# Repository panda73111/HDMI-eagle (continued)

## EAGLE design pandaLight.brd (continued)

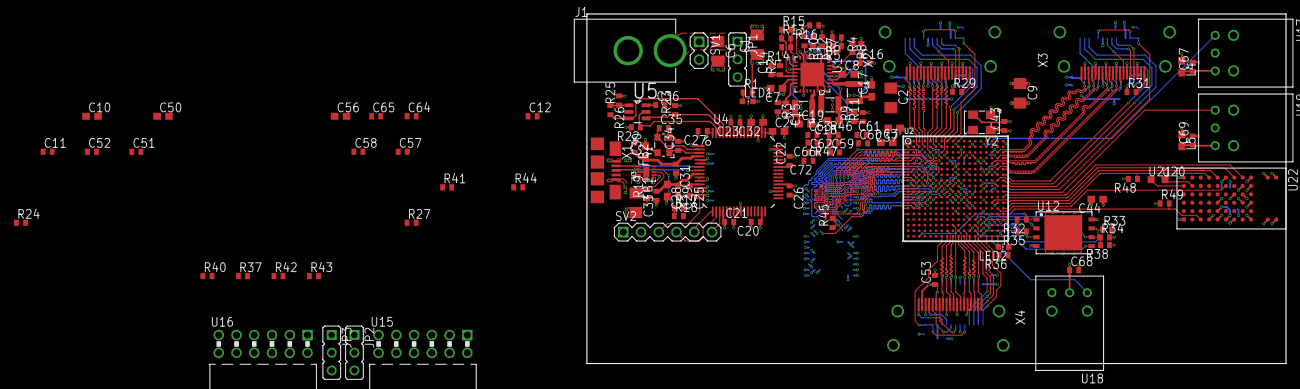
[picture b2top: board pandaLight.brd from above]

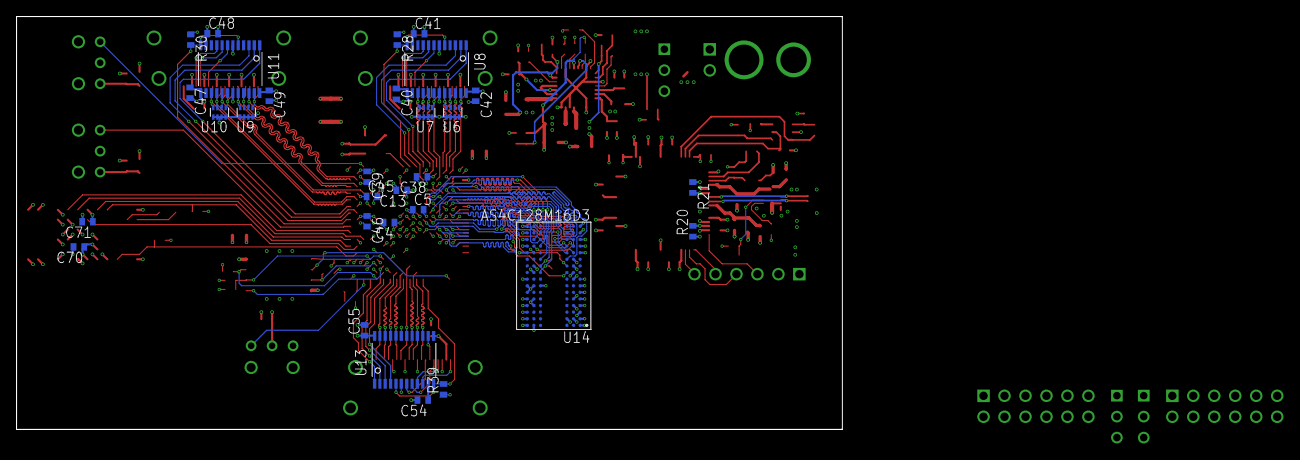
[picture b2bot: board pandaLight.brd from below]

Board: 4 copper layers, 100.0 x 50.0 mm, 164 parts (30 on the bottom side), 172 nets.

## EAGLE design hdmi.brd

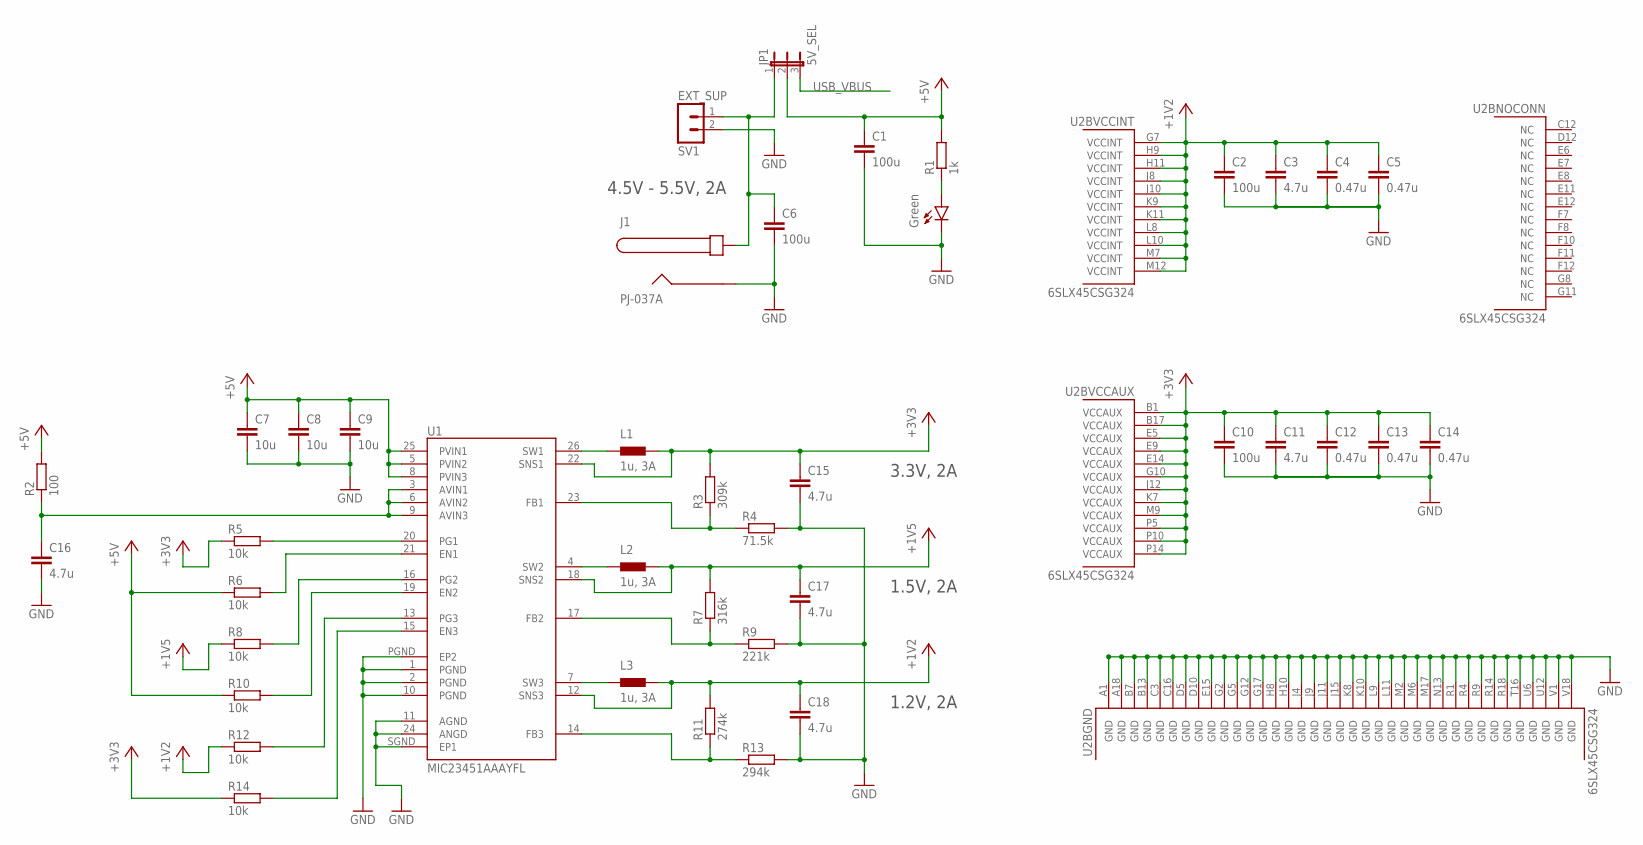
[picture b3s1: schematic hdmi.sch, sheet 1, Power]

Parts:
C1, C2, C6, C10: 100u; 1206
C3, C11, C15, C16, C17, C18: 4.7u; 0402
C4, C5, C12, C13, C14: 0.47u; 0402
C7, C8, C9: 10u; 0402
J1: PJ-037A
JP1: 5V_SEL; JP2
L1, L2, L3: 1u, 3A; 1008
LED1: Green; LED-0603
R1: 1k; 0402
R2: 100; 0402
R3: 309k; 0402
R4: 71.5k; 0402
R5, R6, R8, R10, R12, R14: 10k; 0402
R7: 316k; 0402
R9: 221k; 0402
R11: 274k; 0402
R13: 294k; 0402
SV1: EXT_SUP; MA02-1
U1: MIC23451AAAYFL; QFN-26-4X4
U2: 6SLX45CSG324; CS324

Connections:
+1V2: C2.1, C3.1, C4.1, C5.1, C18.1, L3.2, R11.2, R12.1, U1.12 (SNS3), U2.G7 (VCCINT), U2.H9 (VCCINT), U2.H11 (VCCINT), U2.J8 (VCCINT), U2.J10 (VCCINT), U2.K9 (VCCINT), U2.K11 (VCCINT), U2.L8 (VCCINT), U2.L10 (VCCINT), U2.M7 (VCCINT), U2.M12 (VCCINT)
+1V5: C17.1, L2.2, R7.2, R8.1, U1.18 (SNS2); also elsewhere on the board
+3V3: C10.1, C11.1, C12.1, C13.1, C14.1, C15.1, L1.2, R3.2, R5.1, R14.1, U1.22 (SNS1), U2.B1 (VCCAUX), U2.B17 (VCCAUX), U2.E5 (VCCAUX), U2.E9 (VCCAUX), U2.E14 (VCCAUX), U2.G10 (VCCAUX), U2.J12 (VCCAUX), U2.K7 (VCCAUX), U2.M9 (VCCAUX), U2.P5 (VCCAUX), U2.P10 (VCCAUX), U2.P14 (VCCAUX); also elsewhere on the board
+5V: C1.1, C7.1, C8.1, C9.1, JP1.2, R1.2, R2.2, R6.1, R10.1, U1.5 (PVIN2), U1.8 (PVIN3), U1.25 (PVIN1); also elsewhere on the board
CENTER: C6.1, J1.CENTER, JP1.1, SV1.1
GND: C1.2, C2.2, C3.2, C4.2, C5.2, C6.2, C7.2, C8.2, C9.2, C10.2, C11.2, C12.2, C13.2, C14.2, C15.2, C16.2, C17.2, C18.2, J1.BARREL, LED1.C, R4.2, R9.2, R13.2, SV1.2, U1.1 (PGND), U1.2 (PGND), U1.10 (PGND), U1.11 (AGND), U1.24 (ANGD), U1.PGND (EP2), U1.SGND (EP1), U2.A1 (GND), U2.A18 (GND), U2.B7 (GND), U2.B13 (GND), U2.C3 (GND), U2.C16 (GND), U2.D5 (GND), U2.D10 (GND), U2.E15 (GND), U2.G2 (GND), U2.G5 (GND), U2.G12 (GND), U2.G17 (GND), U2.H8 (GND), U2.H10 (GND), U2.J4 (GND), U2.J9 (GND), U2.J11 (GND), U2.J15 (GND), U2.K8 (GND), U2.K10 (GND), U2.L9 (GND), U2.L11 (GND), U2.M2 (GND), U2.M6 (GND), U2.M17 (GND), U2.N13 (GND), U2.R1 (GND), U2.R4 (GND), U2.R9 (GND), U2.R14 (GND), U2.R18 (GND), U2.T16 (GND), U2.U6 (GND), U2.U12 (GND), U2.V1 (GND), U2.V18 (GND); also elsewhere on the board
unnamed: L1.1, U1.26 (SW1)
unnamed: C16.1, R2.1, U1.3 (AVIN1), U1.6 (AVIN2), U1.9 (AVIN3)
unnamed: L2.1, U1.4 (SW2)
unnamed: L3.1, U1.7 (SW3)
unnamed: R11.1, R13.1, U1.14 (FB3)
unnamed: R8.2, U1.16 (PG2)
unnamed: R3.1, R4.1, U1.23 (FB1)
unnamed: R5.2, U1.20 (PG1)
unnamed: R7.1, R9.1, U1.17 (FB2)
unnamed: R10.2, U1.19 (EN2)
unnamed: R6.2, U1.21 (EN1)
unnamed: R12.2, U1.13 (PG3)
unnamed: R14.2, U1.15 (EN3)
unnamed: LED1.A, R1.1
USB_VBUS: JP1.3; also elsewhere on the board

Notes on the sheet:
4.5V - 5.5V, 2A
3.3V, 2A
1.5V, 2A
1.2V, 2A

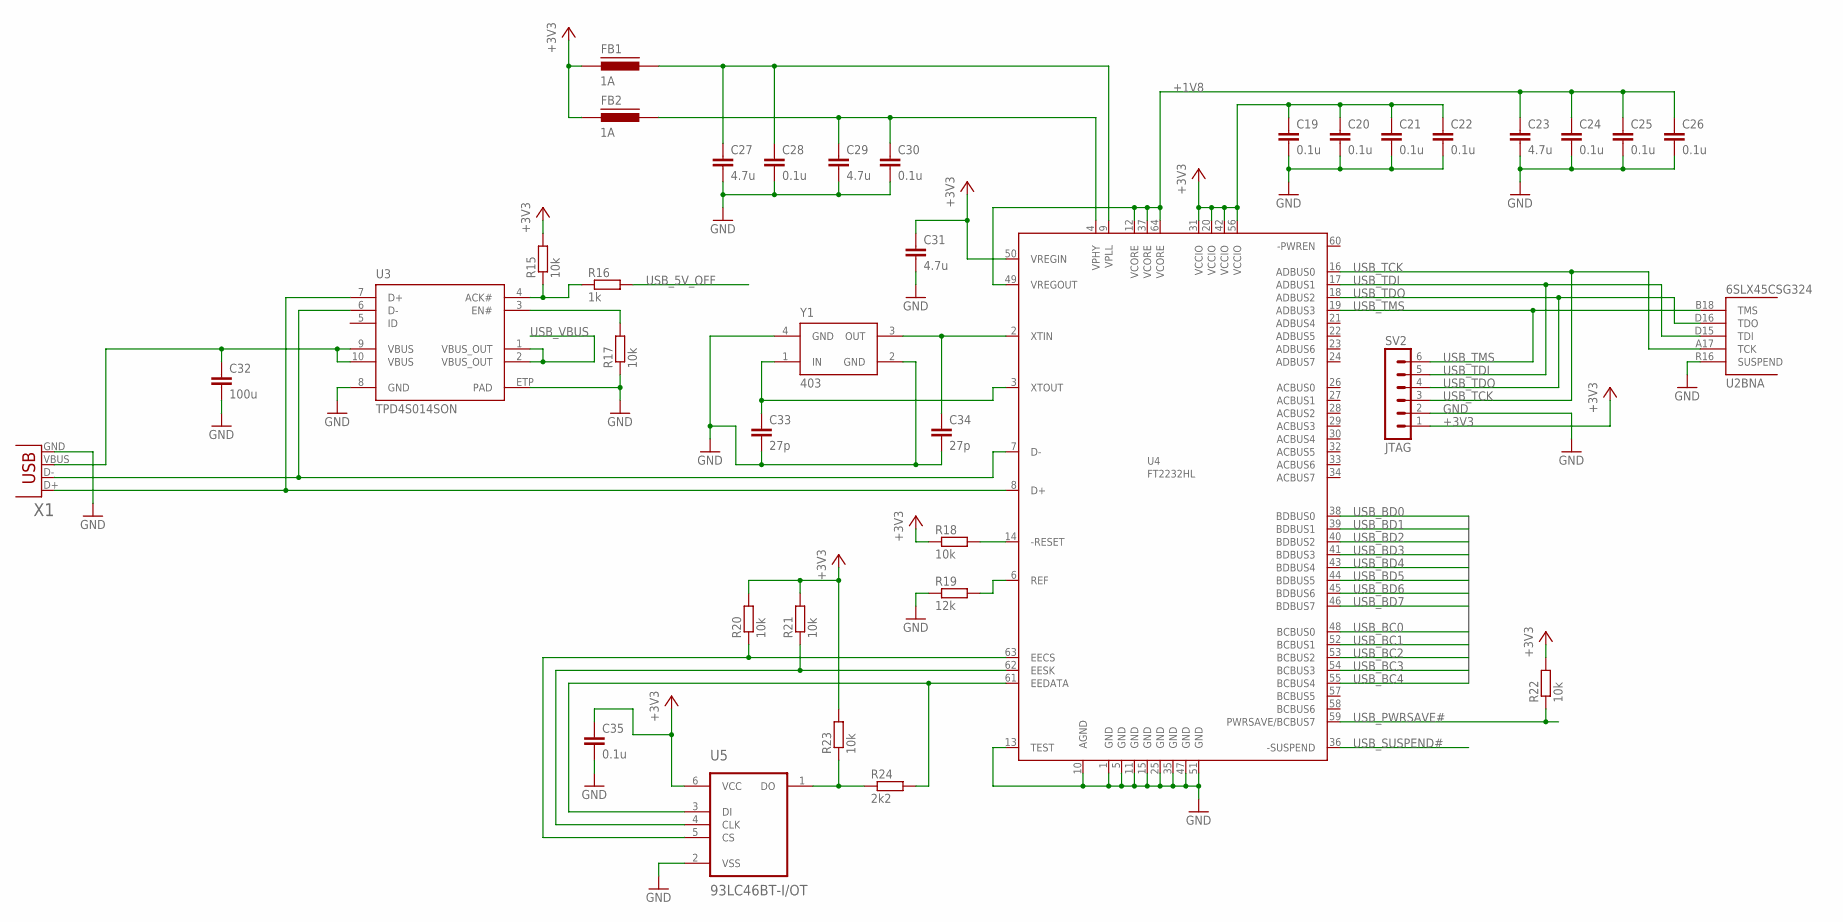
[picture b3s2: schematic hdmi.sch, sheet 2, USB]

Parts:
C19, C20, C21, C22, C24, C25, C26, C28, C30, C35: 0.1u; 0402
C23, C27, C29, C31: 4.7u; 0402
C32: 100u; 1206
C33, C34: 27p; 0402
FB1, FB2: 1A; 0402
R15, R17, R18, R20, R21, R22, R23: 10k; 0402
R16: 1k; 0402
R19: 12k; 0402
R24: 2k2; 0402
SV2: JTAG; MA06-1
U2: 6SLX45CSG324; CS324
U3: TPD4S014SON; SON10
U4: FT2232HL; LQFP64
U5: 93LC46BT-I/OT; SOT23-6
X1: USBUB-S; USB-UB-S
Y1: 403; 403-3.2X2.5

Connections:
+1V8: C23.1, C24.1, C25.1, C26.1, U4.12 (VCORE), U4.37 (VCORE), U4.49 (VREGOUT), U4.64 (VCORE)
+3V3: C19.1, C20.1, C21.1, C22.1, C31.1, C35.1, FB1.1, FB2.1, R15.2, R18.1, R20.2, R21.2, R22.2, R23.2, SV2.1, U4.20 (VCCIO), U4.31 (VCCIO), U4.42 (VCCIO), U4.50 (VREGIN), U4.56 (VCCIO), U5.6 (VCC); also elsewhere on the board
GND: C19.2, C20.2, C21.2, C22.2, C23.2, C24.2, C25.2, C26.2, C27.2, C28.2, C29.2, C30.2, C31.2, C32.2, C33.2, C34.2, C35.2, R17.1, R19.1, SV2.2, U2.R16 (SUSPEND), U3.8 (GND), U3.ETP (PAD), U4.1 (GND), U4.5 (GND), U4.10 (AGND), U4.11 (GND), U4.13 (TEST), U4.15 (GND), U4.25 (GND), U4.35 (GND), U4.47 (GND), U4.51 (GND), U5.2 (VSS), X1.GND, Y1.2 (GND), Y1.4 (GND); also elsewhere on the board
unnamed: C34.1, U4.2 (XTIN), Y1.3 (OUT)
unnamed: C33.1, U4.3 (XTOUT), Y1.1 (IN)
unnamed: R20.1, U4.63 (EECS), U5.5 (CS)
unnamed: U3.6 (D-), U4.7 (D-), X1.D-
unnamed: U3.7 (D+), U4.8 (D+), X1.D+
unnamed: R21.1, U4.62 (EESK), U5.4 (CLK)
unnamed: R24.2, U4.61 (EEDATA), U5.3 (DI)
unnamed: R19.2, U4.6 (REF)
unnamed: R23.1, R24.1, U5.1 (DO)
unnamed: R18.2, U4.14 (-RESET)
unnamed: C29.1, C30.1, FB2.2, U4.4 (VPHY)
unnamed: C27.1, C28.1, FB1.2, U4.9 (VPLL)
unnamed: C32.1, U3.9 (VBUS), U3.10 (VBUS), X1.VBUS
USB_5V_ACK#: R15.1, R16.1, U3.4 (ACK#)
USB_5V_DISABLE: R17.2, U3.3 (EN#)
USB_5V_OFF: R16.2; also elsewhere on the board
USB_BC0: U4.48 (BCBUS0); also elsewhere on the board
USB_BC1: U4.52 (BCBUS1); also elsewhere on the board
USB_BC2: U4.53 (BCBUS2); also elsewhere on the board
USB_BC3: U4.54 (BCBUS3); also elsewhere on the board
USB_BC4: U4.55 (BCBUS4); also elsewhere on the board
USB_BD0: U4.38 (BDBUS0); also elsewhere on the board
USB_BD1: U4.39 (BDBUS1); also elsewhere on the board
USB_BD2: U4.40 (BDBUS2); also elsewhere on the board
USB_BD3: U4.41 (BDBUS3); also elsewhere on the board
USB_BD4: U4.43 (BDBUS4); also elsewhere on the board
USB_BD5: U4.44 (BDBUS5); also elsewhere on the board
USB_BD6: U4.45 (BDBUS6); also elsewhere on the board
USB_BD7: U4.46 (BDBUS7); also elsewhere on the board
USB_PWRSAVE#: R22.1, U4.59 (PWRSAVE/BCBUS7)
USB_SUSPEND#: U4.36 (-SUSPEND); also elsewhere on the board
USB_TCK: SV2.3, U2.A17 (TCK), U4.16 (ADBUS0)
USB_TDI: SV2.5, U2.D15 (TDI), U4.17 (ADBUS1)
USB_TDO: SV2.4, U2.D16 (TDO), U4.18 (ADBUS2)
USB_TMS: SV2.6, U2.B18 (TMS), U4.19 (ADBUS3)
USB_VBUS: U3.1 (VBUS_OUT), U3.2 (VBUS_OUT); also elsewhere on the board

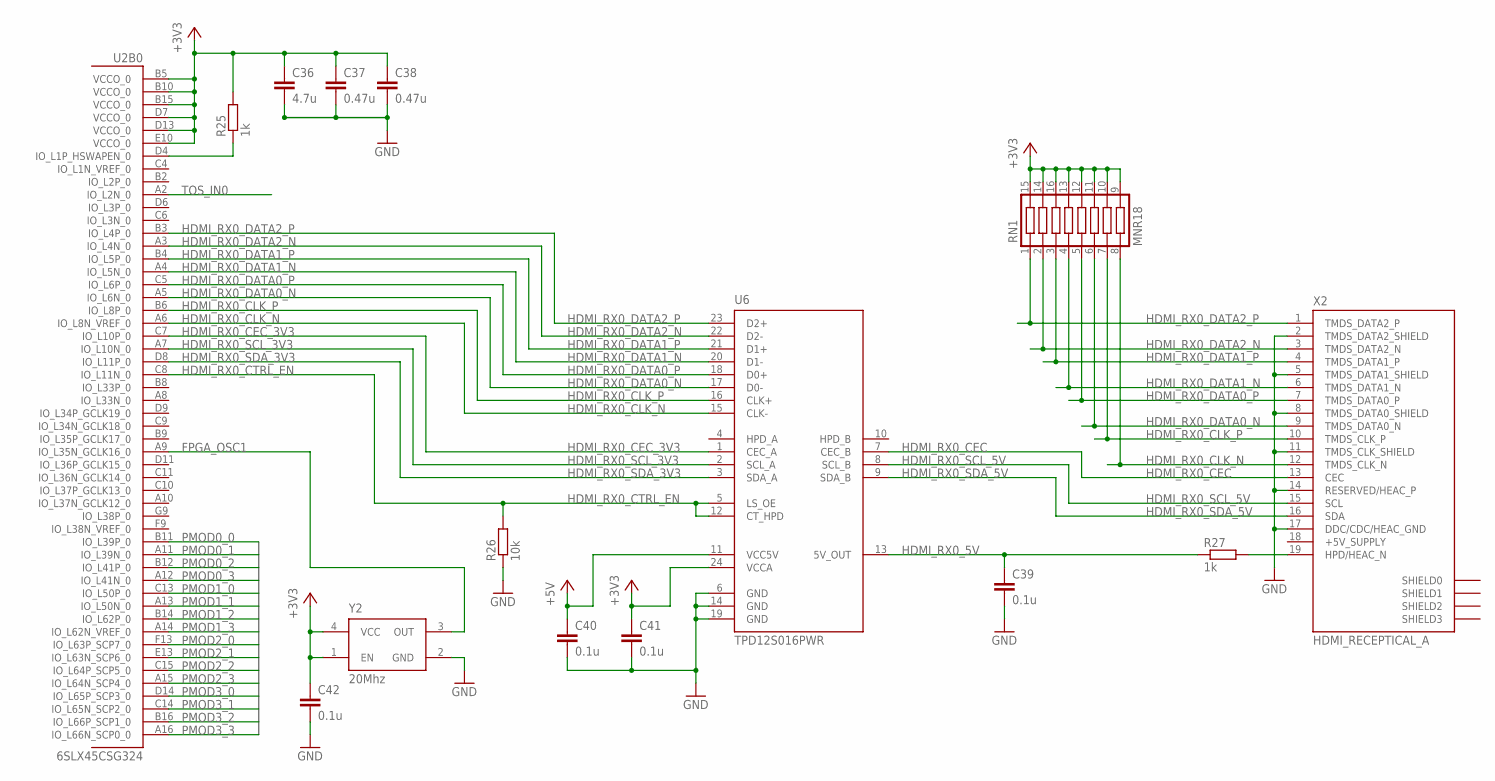
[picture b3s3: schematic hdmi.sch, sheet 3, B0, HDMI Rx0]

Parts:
C36: 4.7u; 0402
C37, C38: 0.47u; 0402
C39, C40, C41, C42: 0.1u; 0402
R25, R27: 1k; 0402
R26: 10k; 0402
RN1: MNR18
U2: 6SLX45CSG324; CS324
U6: TPD12S016PWR; PW_R-PDSO-G24
X2: HDMI_RECEPTICAL_A; HDMI_TYPE_A_RECEPTICAL
Y2: 20Mhz; 636

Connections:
+3V3: C36.1, C37.1, C38.1, C41.1, C42.1, R25.2, RN1.9, RN1.10, RN1.11, RN1.12, RN1.13, RN1.14 (15), RN1.15 (16), RN1.16 (C3), U2.B5 (VCCO_0), U2.B10 (VCCO_0), U2.B15 (VCCO_0), U2.D7 (VCCO_0), U2.D13 (VCCO_0), U2.E10 (VCCO_0), U6.24 (VCCA), Y2.1 (EN), Y2.4 (VCC); also elsewhere on the board
+5V: C40.1, U6.11 (VCC5V); also elsewhere on the board
+5V_SUPPLY: X2.18 (+5V_SUPPLY); also elsewhere on the board
FPGA_OSC1: U2.A9 (IO_L35N_GCLK16_0), Y2.3 (OUT)
GND: C36.2, C37.2, C38.2, C39.2, C40.2, C41.2, C42.2, R26.1, U6.6 (GND), U6.14 (GND), U6.19 (GND), X2.2 (TMDS_DATA2_SHIELD), X2.5 (TMDS_DATA1_SHIELD), X2.8 (TMDS_DATA0_SHIELD), X2.11 (TMDS_CLK_SHIELD), X2.14 (RESERVED/HEAC_P), X2.17 (DDC/CDC/HEAC_GND), Y2.2 (GND); also elsewhere on the board
HDMI_RX0_5V: C39.1, R27.1, U6.13 (5V_OUT)
HDMI_RX0_CEC: U6.7 (CEC_B), X2.13 (CEC)
HDMI_RX0_CEC_3V3: U2.C7 (IO_L10P_0), U6.1 (CEC_A)
HDMI_RX0_CLK_N: RN1.8, U2.A6 (IO_L8N_VREF_0), U6.15 (CLK-), X2.12 (TMDS_CLK_N)
HDMI_RX0_CLK_P: RN1.7, U2.B6 (IO_L8P_0), U6.16 (CLK+), X2.10 (TMDS_CLK_P)
HDMI_RX0_CTRL_EN: R26.2, U2.C8 (IO_L11N_0), U6.5 (LS_OE), U6.12 (CT_HPD)
HDMI_RX0_DATA0_N: RN1.6, U2.A5 (IO_L6N_0), U6.17 (D0-), X2.9 (TMDS_DATA0_N)
HDMI_RX0_DATA0_P: RN1.5, U2.C5 (IO_L6P_0), U6.18 (D0+), X2.7 (TMDS_DATA0_P)
HDMI_RX0_DATA1_N: RN1.4, U2.A4 (IO_L5N_0), U6.20 (D1-), X2.6 (TMDS_DATA1_N)
HDMI_RX0_DATA1_P: RN1.3, U2.B4 (IO_L5P_0), U6.21 (D1+), X2.4 (TMDS_DATA1_P)
HDMI_RX0_DATA2_N: RN1.2, U2.A3 (IO_L4N_0), U6.22 (D2-), X2.3 (TMDS_DATA2_N)
HDMI_RX0_DATA2_P: RN1.1, U2.B3 (IO_L4P_0), U6.23 (D2+), X2.1 (TMDS_DATA2_P)
HDMI_RX0_SCL_3V3: U2.A7 (IO_L10N_0), U6.2 (SCL_A)
HDMI_RX0_SCL_5V: U6.8 (SCL_B), X2.15 (SCL)
HDMI_RX0_SDA_3V3: U2.D8 (IO_L11P_0), U6.3 (SDA_A)
HDMI_RX0_SDA_5V: U6.9 (SDA_B), X2.16 (SDA)
unnamed: R25.1, U2.D4 (IO_L1P_HSWAPEN_0)
unnamed: R27.2, X2.19 (HPD/HEAC_N)
PMOD0_0: U2.B11 (IO_L39P_0); also elsewhere on the board
PMOD0_1: U2.A11 (IO_L39N_0); also elsewhere on the board
PMOD0_2: U2.B12 (IO_L41P_0); also elsewhere on the board
PMOD0_3: U2.A12 (IO_L41N_0); also elsewhere on the board
PMOD1_0: U2.C13 (IO_L50P_0); also elsewhere on the board
PMOD1_1: U2.A13 (IO_L50N_0); also elsewhere on the board
PMOD1_2: U2.B14 (IO_L62P_0); also elsewhere on the board
PMOD1_3: U2.A14 (IO_L62N_VREF_0); also elsewhere on the board
PMOD2_0: U2.F13 (IO_L63P_SCP7_0); also elsewhere on the board
PMOD2_1: U2.E13 (IO_L63N_SCP6_0); also elsewhere on the board
PMOD2_2: U2.C15 (IO_L64P_SCP5_0); also elsewhere on the board
PMOD2_3: U2.A15 (IO_L64N_SCP4_0); also elsewhere on the board
PMOD3_0: U2.D14 (IO_L65P_SCP3_0); also elsewhere on the board
PMOD3_1: U2.C14 (IO_L65N_SCP2_0); also elsewhere on the board
PMOD3_2: U2.B16 (IO_L66P_SCP1_0); also elsewhere on the board
PMOD3_3: U2.A16 (IO_L66N_SCP0_0); also elsewhere on the board
TOS_IN0: U2.A2 (IO_L2N_0); also elsewhere on the board

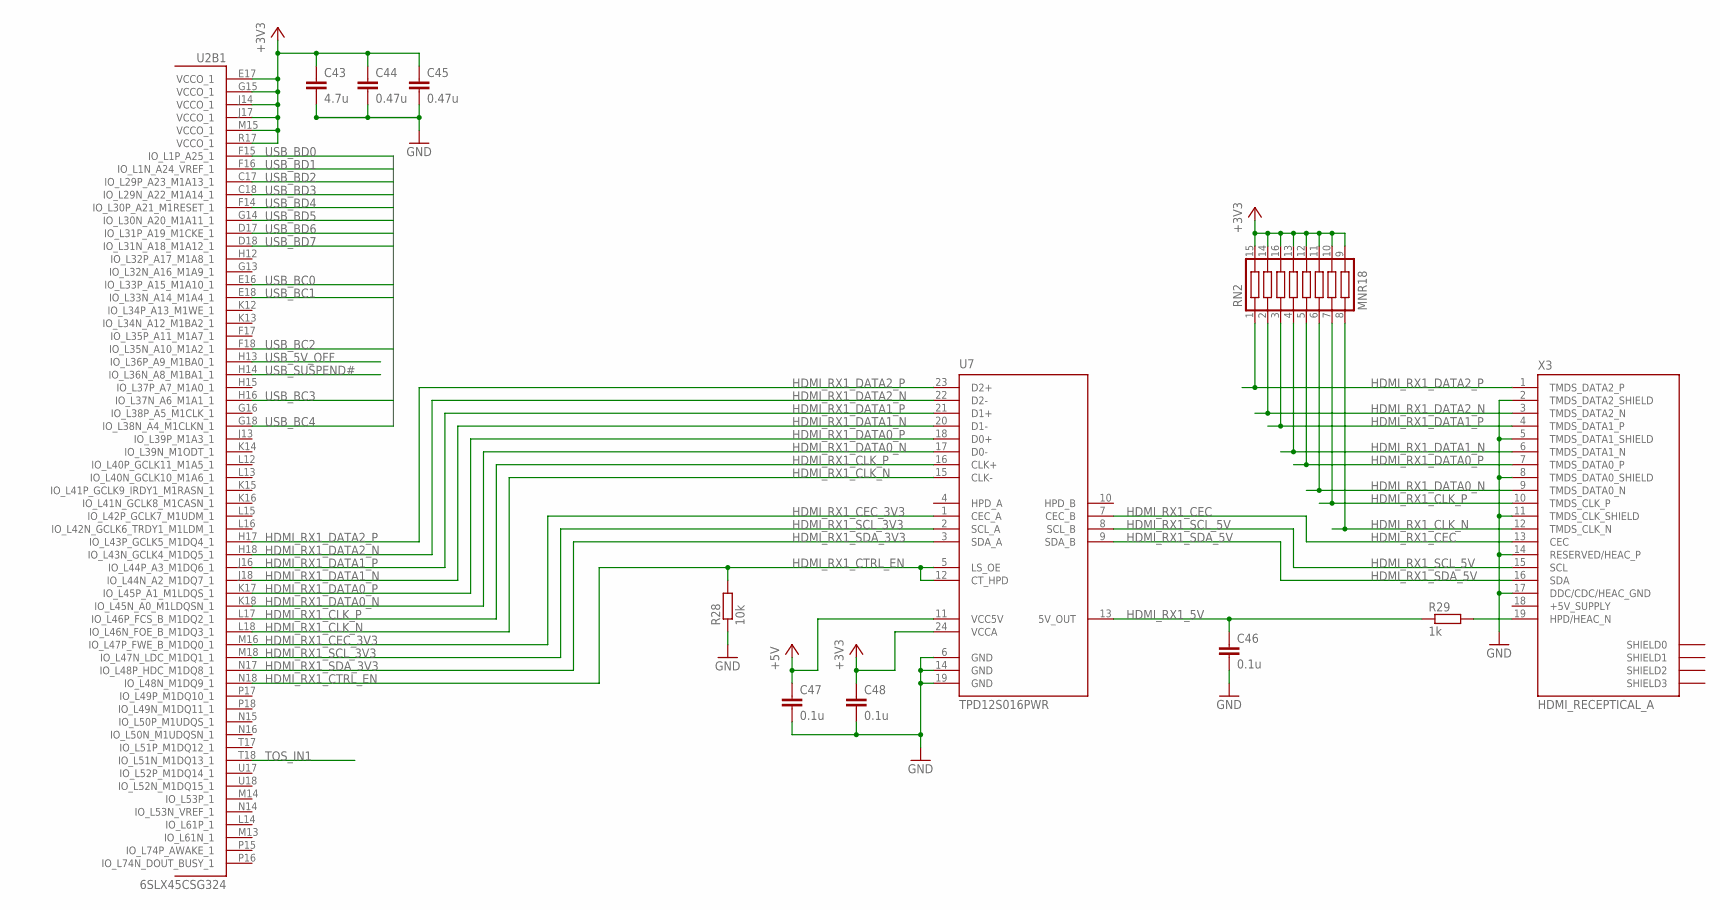
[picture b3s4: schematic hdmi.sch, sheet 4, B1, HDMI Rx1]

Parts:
C43: 4.7u; 0402
C44, C45: 0.47u; 0402
C46, C47, C48: 0.1u; 0402
R28: 10k; 0402
R29: 1k; 0402
RN2: MNR18
U2: 6SLX45CSG324; CS324
U7: TPD12S016PWR; PW_R-PDSO-G24
X3: HDMI_RECEPTICAL_A; HDMI_TYPE_A_RECEPTICAL

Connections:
+3V3: C43.1, C44.1, C45.1, C48.1, RN2.9, RN2.10, RN2.11, RN2.12, RN2.13, RN2.14 (15), RN2.15 (16), RN2.16 (C3), U2.E17 (VCCO_1), U2.G15 (VCCO_1), U2.J14 (VCCO_1), U2.J17 (VCCO_1), U2.M15 (VCCO_1), U2.R17 (VCCO_1), U7.24 (VCCA); also elsewhere on the board
+5V: C47.1, U7.11 (VCC5V); also elsewhere on the board
+5V_SUPPLY: X3.18 (+5V_SUPPLY); also elsewhere on the board
GND: C43.2, C44.2, C45.2, C46.2, C47.2, C48.2, R28.1, U7.6 (GND), U7.14 (GND), U7.19 (GND), X3.2 (TMDS_DATA2_SHIELD), X3.5 (TMDS_DATA1_SHIELD), X3.8 (TMDS_DATA0_SHIELD), X3.11 (TMDS_CLK_SHIELD), X3.14 (RESERVED/HEAC_P), X3.17 (DDC/CDC/HEAC_GND); also elsewhere on the board
HDMI_RX1_5V: C46.1, R29.1, U7.13 (5V_OUT)
HDMI_RX1_CEC: U7.7 (CEC_B), X3.13 (CEC)
HDMI_RX1_CEC_3V3: U2.M16 (IO_L47P_FWE_B_M1DQ0_1), U7.1 (CEC_A)
HDMI_RX1_CLK_N: RN2.8, U2.L18 (IO_L46N_FOE_B_M1DQ3_1), U7.15 (CLK-), X3.12 (TMDS_CLK_N)
HDMI_RX1_CLK_P: RN2.7, U2.L17 (IO_L46P_FCS_B_M1DQ2_1), U7.16 (CLK+), X3.10 (TMDS_CLK_P)
HDMI_RX1_CTRL_EN: R28.2, U2.N18 (IO_L48N_M1DQ9_1), U7.5 (LS_OE), U7.12 (CT_HPD)
HDMI_RX1_DATA0_N: RN2.6, U2.K18 (IO_L45N_A0_M1LDQSN_1), U7.17 (D0-), X3.9 (TMDS_DATA0_N)
HDMI_RX1_DATA0_P: RN2.5, U2.K17 (IO_L45P_A1_M1LDQS_1), U7.18 (D0+), X3.7 (TMDS_DATA0_P)
HDMI_RX1_DATA1_N: RN2.4, U2.J18 (IO_L44N_A2_M1DQ7_1), U7.20 (D1-), X3.6 (TMDS_DATA1_N)
HDMI_RX1_DATA1_P: RN2.3, U2.J16 (IO_L44P_A3_M1DQ6_1), U7.21 (D1+), X3.4 (TMDS_DATA1_P)
HDMI_RX1_DATA2_N: RN2.2, U2.H18 (IO_L43N_GCLK4_M1DQ5_1), U7.22 (D2-), X3.3 (TMDS_DATA2_N)
HDMI_RX1_DATA2_P: RN2.1, U2.H17 (IO_L43P_GCLK5_M1DQ4_1), U7.23 (D2+), X3.1 (TMDS_DATA2_P)
HDMI_RX1_SCL_3V3: U2.M18 (IO_L47N_LDC_M1DQ1_1), U7.2 (SCL_A)
HDMI_RX1_SCL_5V: U7.8 (SCL_B), X3.15 (SCL)
HDMI_RX1_SDA_3V3: U2.N17 (IO_L48P_HDC_M1DQ8_1), U7.3 (SDA_A)
HDMI_RX1_SDA_5V: U7.9 (SDA_B), X3.16 (SDA)
unnamed: R29.2, X3.19 (HPD/HEAC_N)
TOS_IN1: U2.T18 (IO_L51N_M1DQ13_1); also elsewhere on the board
USB_5V_OFF: U2.H13 (IO_L36P_A9_M1BA0_1); also elsewhere on the board
USB_BC0: U2.E16 (IO_L33P_A15_M1A10_1); also elsewhere on the board
USB_BC1: U2.E18 (IO_L33N_A14_M1A4_1); also elsewhere on the board
USB_BC2: U2.F18 (IO_L35N_A10_M1A2_1); also elsewhere on the board
USB_BC3: U2.H16 (IO_L37N_A6_M1A1_1); also elsewhere on the board
USB_BC4: U2.G18 (IO_L38N_A4_M1CLKN_1); also elsewhere on the board
USB_BD0: U2.F15 (IO_L1P_A25_1); also elsewhere on the board
USB_BD1: U2.F16 (IO_L1N_A24_VREF_1); also elsewhere on the board
USB_BD2: U2.C17 (IO_L29P_A23_M1A13_1); also elsewhere on the board
USB_BD3: U2.C18 (IO_L29N_A22_M1A14_1); also elsewhere on the board
USB_BD4: U2.F14 (IO_L30P_A21_M1RESET_1); also elsewhere on the board
USB_BD5: U2.G14 (IO_L30N_A20_M1A11_1); also elsewhere on the board
USB_BD6: U2.D17 (IO_L31P_A19_M1CKE_1); also elsewhere on the board
USB_BD7: U2.D18 (IO_L31N_A18_M1A12_1); also elsewhere on the board
USB_SUSPEND#: U2.H14 (IO_L36N_A8_M1BA1_1); also elsewhere on the board

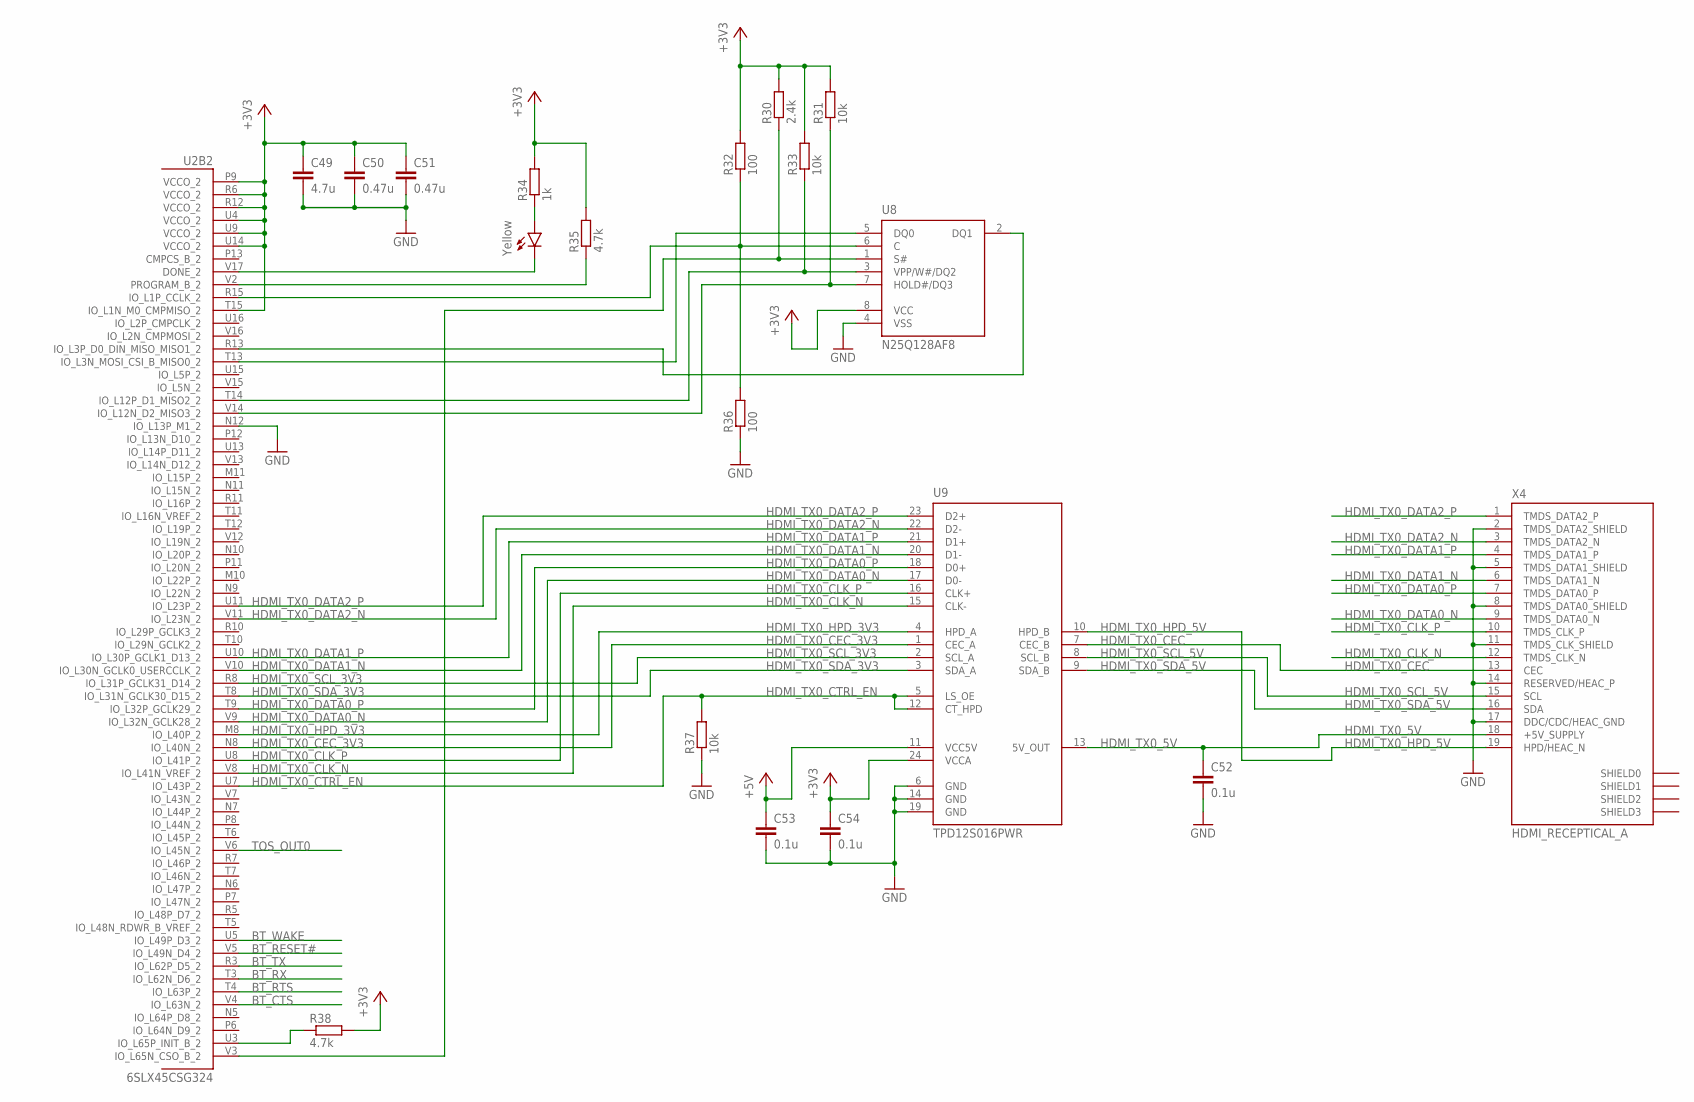
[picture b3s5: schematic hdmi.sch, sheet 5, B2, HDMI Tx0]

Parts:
C49: 4.7u; 0402
C50, C51: 0.47u; 0402
C52, C53, C54: 0.1u; 0402
LED2: Yellow; LED-0603
R30: 2.4k; 0402
R31, R33, R37: 10k; 0402
R32, R36: 100; 0402
R34: 1k; 0402
R35, R38: 4.7k; 0402
U2: 6SLX45CSG324; CS324
U8: N25Q128AF8; V-PDFN-8_8X6
U9: TPD12S016PWR; PW_R-PDSO-G24
X4: HDMI_RECEPTICAL_A; HDMI_TYPE_A_RECEPTICAL

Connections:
+3V3: C49.1, C50.1, C51.1, C54.1, R30.2, R31.2, R32.2, R33.2, R34.2, R35.2, R38.2, U2.P9 (VCCO_2), U2.R6 (VCCO_2), U2.R12 (VCCO_2), U2.T15 (IO_L1N_M0_CMPMISO_2), U2.U4 (VCCO_2), U2.U9 (VCCO_2), U2.U14 (VCCO_2), U8.8 (VCC), U9.24 (VCCA); also elsewhere on the board
+5V: C53.1, U9.11 (VCC5V); also elsewhere on the board
BT_CTS: U2.V4 (IO_L63N_2); also elsewhere on the board
BT_RESET#: U2.V5 (IO_L49N_D4_2); also elsewhere on the board
BT_RTS: U2.T4 (IO_L63P_2); also elsewhere on the board
BT_RX: U2.T3 (IO_L62N_D6_2); also elsewhere on the board
BT_TX: U2.R3 (IO_L62P_D5_2); also elsewhere on the board
BT_WAKE: U2.U5 (IO_L49P_D3_2); also elsewhere on the board
GND: C49.2, C50.2, C51.2, C52.2, C53.2, C54.2, R36.1, R37.1, U2.N12 (IO_L13P_M1_2), U8.4 (VSS), U9.6 (GND), U9.14 (GND), U9.19 (GND), X4.2 (TMDS_DATA2_SHIELD), X4.5 (TMDS_DATA1_SHIELD), X4.8 (TMDS_DATA0_SHIELD), X4.11 (TMDS_CLK_SHIELD), X4.14 (RESERVED/HEAC_P), X4.17 (DDC/CDC/HEAC_GND); also elsewhere on the board
HDMI_TX0_5V: C52.1, U9.13 (5V_OUT), X4.18 (+5V_SUPPLY)
HDMI_TX0_CEC: U9.7 (CEC_B), X4.13 (CEC)
HDMI_TX0_CEC_3V3: U2.N8 (IO_L40N_2), U9.1 (CEC_A)
HDMI_TX0_CLK_N: U2.V8 (IO_L41N_VREF_2), U9.15 (CLK-), X4.12 (TMDS_CLK_N)
HDMI_TX0_CLK_P: U2.U8 (IO_L41P_2), U9.16 (CLK+), X4.10 (TMDS_CLK_P)
HDMI_TX0_CTRL_EN: R37.2, U2.U7 (IO_L43P_2), U9.5 (LS_OE), U9.12 (CT_HPD)
HDMI_TX0_DATA0_N: U2.V9 (IO_L32N_GCLK28_2), U9.17 (D0-), X4.9 (TMDS_DATA0_N)
HDMI_TX0_DATA0_P: U2.T9 (IO_L32P_GCLK29_2), U9.18 (D0+), X4.7 (TMDS_DATA0_P)
HDMI_TX0_DATA1_N: U2.V10 (IO_L30N_GCLK0_USERCCLK_2), U9.20 (D1-), X4.6 (TMDS_DATA1_N)
HDMI_TX0_DATA1_P: U2.U10 (IO_L30P_GCLK1_D13_2), U9.21 (D1+), X4.4 (TMDS_DATA1_P)
HDMI_TX0_DATA2_N: U2.V11 (IO_L23N_2), U9.22 (D2-), X4.3 (TMDS_DATA2_N)
HDMI_TX0_DATA2_P: U2.U11 (IO_L23P_2), U9.23 (D2+), X4.1 (TMDS_DATA2_P)
HDMI_TX0_HPD_3V3: U2.M8 (IO_L40P_2), U9.4 (HPD_A)
HDMI_TX0_HPD_5V: U9.10 (HPD_B), X4.19 (HPD/HEAC_N)
HDMI_TX0_SCL_3V3: U2.R8 (IO_L31P_GCLK31_D14_2), U9.2 (SCL_A)
HDMI_TX0_SCL_5V: U9.8 (SCL_B), X4.15 (SCL)
HDMI_TX0_SDA_3V3: U2.T8 (IO_L31N_GCLK30_D15_2), U9.3 (SDA_A)
HDMI_TX0_SDA_5V: U9.9 (SDA_B), X4.16 (SDA)
unnamed: LED2.C, U2.V17 (DONE_2)
unnamed: R35.1, U2.V2 (PROGRAM_B_2)
unnamed: LED2.A, R34.1
unnamed: R38.1, U2.U3 (IO_L65P_INIT_B_2)
unnamed: U2.T13 (IO_L3N_MOSI_CSI_B_MISO0_2), U8.5 (DQ0)
unnamed: R30.1, U2.V3 (IO_L65N_CSO_B_2), U8.1 (S#)
unnamed: R32.1, R36.2, U2.R15 (IO_L1P_CCLK_2), U8.6 (C)
unnamed: U2.R13 (IO_L3P_D0_DIN_MISO_MISO1_2), U8.2 (DQ1)
unnamed: R33.1, U2.T14 (IO_L12P_D1_MISO2_2), U8.3 (VPP/W#/DQ2)
unnamed: R31.1, U2.V14 (IO_L12N_D2_MISO3_2), U8.7 (HOLD#/DQ3)
TOS_OUT0: U2.V6 (IO_L45N_2); also elsewhere on the board

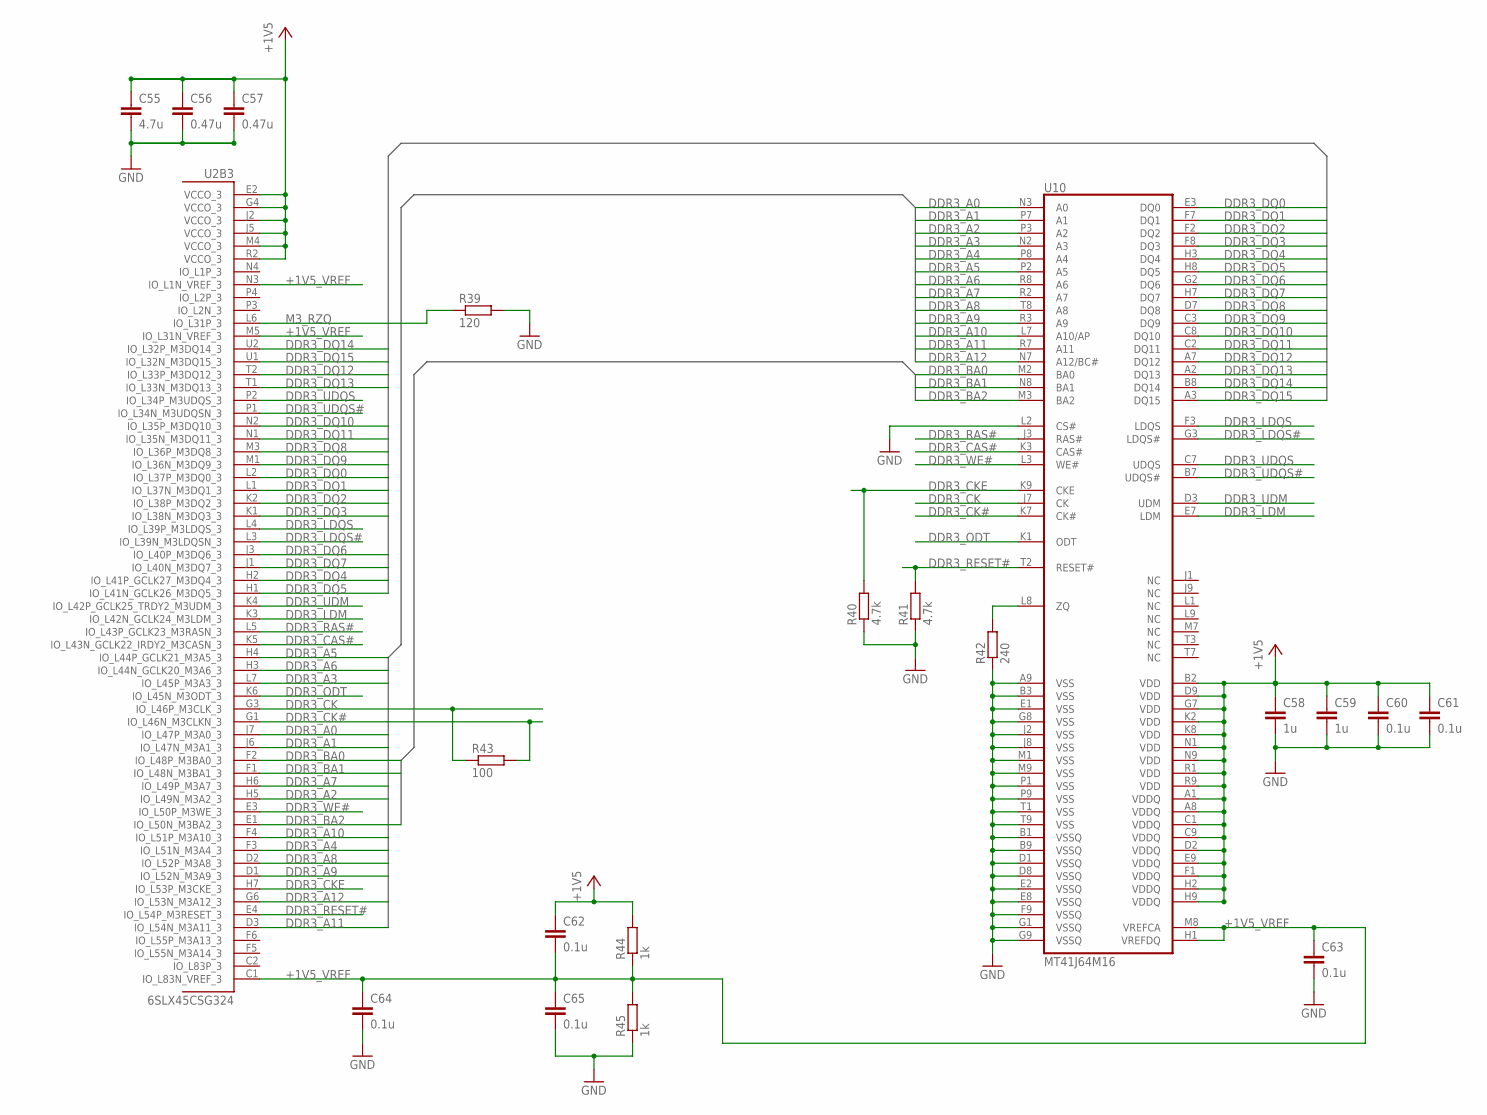
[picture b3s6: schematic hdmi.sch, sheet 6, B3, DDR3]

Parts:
C55: 4.7u; 0402
C56, C57: 0.47u; 0402
C58, C59: 1u; 0402
C60, C61, C62, C63, C64, C65: 0.1u; 0402
R39: 120; 0402
R40, R41: 4.7k; 0402
R42: 240; 0402
R43: 100; 0402
R44, R45: 1k; 0402
U2: 6SLX45CSG324; CS324
U10: MT41J64M16; FBGA96-JT

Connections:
+1V5: C55.1, C56.1, C57.1, C58.1, C59.1, C60.1, C61.1, C62.1, R44.2, U2.E2 (VCCO_3), U2.G4 (VCCO_3), U2.J2 (VCCO_3), U2.J5 (VCCO_3), U2.M4 (VCCO_3), U2.R2 (VCCO_3), U10.A1 (VDDQ), U10.A8 (VDDQ), U10.B2 (VDD), U10.C1 (VDDQ), U10.C9 (VDDQ), U10.D2 (VDDQ), U10.D9 (VDD), U10.E9 (VDDQ), U10.F1 (VDDQ), U10.G7 (VDD), U10.H2 (VDDQ), U10.H9 (VDDQ), U10.K2 (VDD), U10.K8 (VDD), U10.N1 (VDD), U10.N9 (VDD), U10.R1 (VDD), U10.R9 (VDD); also elsewhere on the board
+1V5_VREF: C62.2, C63.1, C64.1, C65.1, R44.1, R45.2, U2.C1 (IO_L83N_VREF_3), U2.M5 (IO_L31N_VREF_3), U2.N3 (IO_L1N_VREF_3), U10.H1 (VREFDQ), U10.M8 (VREFCA)
DDR3_A0: U2.J7 (IO_L47P_M3A0_3), U10.N3 (A0)
DDR3_A1: U2.J6 (IO_L47N_M3A1_3), U10.P7 (A1)
DDR3_A2: U2.H5 (IO_L49N_M3A2_3), U10.P3 (A2)
DDR3_A3: U2.L7 (IO_L45P_M3A3_3), U10.N2 (A3)
DDR3_A4: U2.F3 (IO_L51N_M3A4_3), U10.P8 (A4)
DDR3_A5: U2.H4 (IO_L44P_GCLK21_M3A5_3), U10.P2 (A5)
DDR3_A6: U2.H3 (IO_L44N_GCLK20_M3A6_3), U10.R8 (A6)
DDR3_A7: U2.H6 (IO_L49P_M3A7_3), U10.R2 (A7)
DDR3_A8: U2.D2 (IO_L52P_M3A8_3), U10.T8 (A8)
DDR3_A9: U2.D1 (IO_L52N_M3A9_3), U10.R3 (A9)
DDR3_A10: U2.F4 (IO_L51P_M3A10_3), U10.L7 (A10/AP)
DDR3_A11: U2.D3 (IO_L54N_M3A11_3), U10.R7 (A11)
DDR3_A12: U2.G6 (IO_L53N_M3A12_3), U10.N7 (A12/BC#)
DDR3_BA0: U2.F2 (IO_L48P_M3BA0_3), U10.M2 (BA0)
DDR3_BA1: U2.F1 (IO_L48N_M3BA1_3), U10.N8 (BA1)
DDR3_BA2: U2.E1 (IO_L50N_M3BA2_3), U10.M3 (BA2)
DDR3_CAS#: U2.K5 (IO_L43N_GCLK22_IRDY2_M3CASN_3), U10.K3 (CAS#)
DDR3_CK: R43.1, U2.G3 (IO_L46P_M3CLK_3), U10.J7 (CK)
DDR3_CK#: R43.2, U2.G1 (IO_L46N_M3CLKN_3), U10.K7 (CK#)
DDR3_CKE: R40.2, U2.H7 (IO_L53P_M3CKE_3), U10.K9 (CKE)
DDR3_DQ0: U2.L2 (IO_L37P_M3DQ0_3), U10.E3 (DQ0)
DDR3_DQ1: U2.L1 (IO_L37N_M3DQ1_3), U10.F7 (DQ1)
DDR3_DQ2: U2.K2 (IO_L38P_M3DQ2_3), U10.F2 (DQ2)
DDR3_DQ3: U2.K1 (IO_L38N_M3DQ3_3), U10.F8 (DQ3)
DDR3_DQ4: U2.H2 (IO_L41P_GCLK27_M3DQ4_3), U10.H3 (DQ4)
DDR3_DQ5: U2.H1 (IO_L41N_GCLK26_M3DQ5_3), U10.H8 (DQ5)
DDR3_DQ6: U2.J3 (IO_L40P_M3DQ6_3), U10.G2 (DQ6)
DDR3_DQ7: U2.J1 (IO_L40N_M3DQ7_3), U10.H7 (DQ7)
DDR3_DQ8: U2.M3 (IO_L36P_M3DQ8_3), U10.D7 (DQ8)
DDR3_DQ9: U2.M1 (IO_L36N_M3DQ9_3), U10.C3 (DQ9)
DDR3_DQ10: U2.N2 (IO_L35P_M3DQ10_3), U10.C8 (DQ10)
DDR3_DQ11: U2.N1 (IO_L35N_M3DQ11_3), U10.C2 (DQ11)
DDR3_DQ12: U2.T2 (IO_L33P_M3DQ12_3), U10.A7 (DQ12)
DDR3_DQ13: U2.T1 (IO_L33N_M3DQ13_3), U10.A2 (DQ13)
DDR3_DQ14: U2.U2 (IO_L32P_M3DQ14_3), U10.B8 (DQ14)
DDR3_DQ15: U2.U1 (IO_L32N_M3DQ15_3), U10.A3 (DQ15)
DDR3_LDM: U2.K3 (IO_L42N_GCLK24_M3LDM_3), U10.E7 (LDM)
DDR3_LDQS: U2.L4 (IO_L39P_M3LDQS_3), U10.F3 (LDQS)
DDR3_LDQS#: U2.L3 (IO_L39N_M3LDQSN_3), U10.G3 (LDQS#)
DDR3_ODT: U2.K6 (IO_L45N_M3ODT_3), U10.K1 (ODT)
DDR3_RAS#: U2.L5 (IO_L43P_GCLK23_M3RASN_3), U10.J3 (RAS#)
DDR3_RESET#: R41.2, U2.E4 (IO_L54P_M3RESET_3), U10.T2 (RESET#)
DDR3_UDM: U2.K4 (IO_L42P_GCLK25_TRDY2_M3UDM_3), U10.D3 (UDM)
DDR3_UDQS: U2.P2 (IO_L34P_M3UDQS_3), U10.C7 (UDQS)
DDR3_UDQS#: U2.P1 (IO_L34N_M3UDQSN_3), U10.B7 (UDQS#)
DDR3_WE#: U2.E3 (IO_L50P_M3WE_3), U10.L3 (WE#)
GND: C55.2, C56.2, C57.2, C58.2, C59.2, C60.2, C61.2, C63.2, C64.2, C65.2, R39.2, R40.1, R41.1, R42.1, R45.1, U10.A9 (VSS), U10.B1 (VSSQ), U10.B3 (VSS), U10.B9 (VSSQ), U10.D1 (VSSQ), U10.D8 (VSSQ), U10.E1 (VSS), U10.E2 (VSSQ), U10.E8 (VSSQ), U10.F9 (VSSQ), U10.G1 (VSSQ), U10.G8 (VSS), U10.G9 (VSSQ), U10.J2 (VSS), U10.J8 (VSS), U10.L2 (CS#), U10.M1 (VSS), U10.M9 (VSS), U10.P1 (VSS), U10.P9 (VSS), U10.T1 (VSS), U10.T9 (VSS); also elsewhere on the board
M3_RZQ: R39.1, U2.L6 (IO_L31P_3)
unnamed: R42.2, U10.L8 (ZQ)

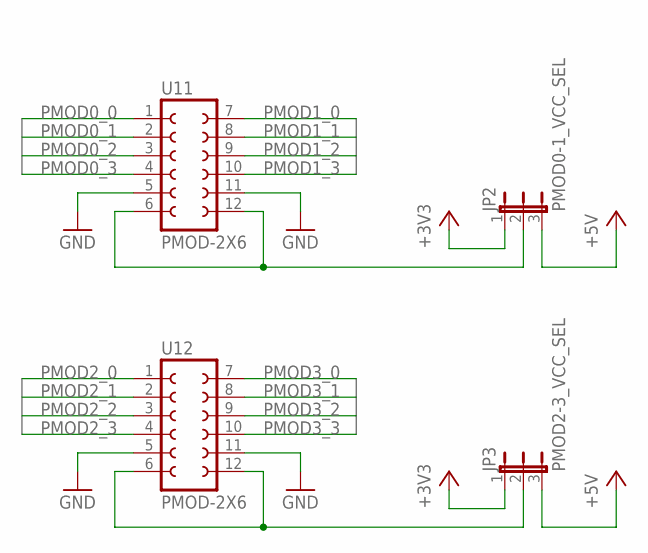
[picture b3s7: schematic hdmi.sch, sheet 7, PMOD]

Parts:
JP2: PMOD0-1_VCC_SEL; JP2
JP3: PMOD2-3_VCC_SEL; JP2
U11, U12: PMOD-2X6

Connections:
+3V3: JP2.1, JP3.1; also elsewhere on the board
+5V: JP2.3, JP3.3; also elsewhere on the board
GND: U11.5, U11.11, U12.5, U12.11; also elsewhere on the board
unnamed: JP3.2, U12.6, U12.12
unnamed: JP2.2, U11.6, U11.12
PMOD0_0: U11.1; also elsewhere on the board
PMOD0_1: U11.2; also elsewhere on the board
PMOD0_2: U11.3; also elsewhere on the board
PMOD0_3: U11.4; also elsewhere on the board
PMOD1_0: U11.7; also elsewhere on the board
PMOD1_1: U11.8; also elsewhere on the board
PMOD1_2: U11.9; also elsewhere on the board
PMOD1_3: U11.10; also elsewhere on the board
PMOD2_0: U12.1; also elsewhere on the board
PMOD2_1: U12.2; also elsewhere on the board
PMOD2_2: U12.3; also elsewhere on the board
PMOD2_3: U12.4; also elsewhere on the board
PMOD3_0: U12.7; also elsewhere on the board
PMOD3_1: U12.8; also elsewhere on the board
PMOD3_2: U12.9; also elsewhere on the board
PMOD3_3: U12.10; also elsewhere on the board
